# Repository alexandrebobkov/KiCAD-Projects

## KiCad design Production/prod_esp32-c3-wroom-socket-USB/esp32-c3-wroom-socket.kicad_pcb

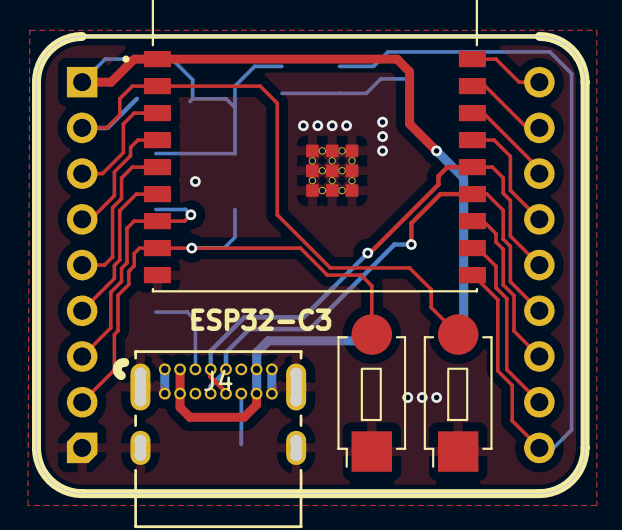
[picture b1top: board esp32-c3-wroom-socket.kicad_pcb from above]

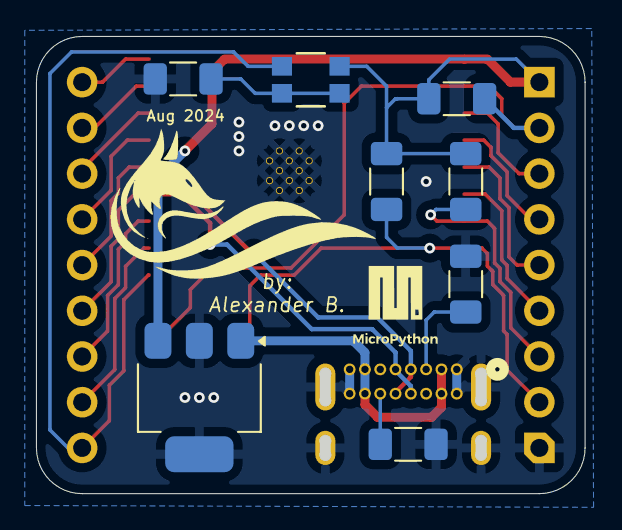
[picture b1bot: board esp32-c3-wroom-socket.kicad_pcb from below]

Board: 2 copper layers, 30.5 x 25.4 mm, 13 parts (8 on the bottom side), 22 nets.

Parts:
J2: Conn_ESP32-C3-WROOM-02
J4: USB-C_Receptacle_Data_16P_GCT-USB4085; USB-C GCT CONN16_USB4085-GF-A
LED1: LED-RED-GREEN-B1552USUG20D; B1552_HVK-M
R1: 10k; R_1206_3216Metric_Pad1.30x1.75mm_HandSolder
R4, R9, R10: 5k1; R_1206_3216Metric_Pad1.30x1.75mm_HandSolder
R7, R8: 2K2; R_1206_3216Metric_Pad1.30x1.75mm_HandSolder
SW1, SW2: SW_Push_SMD_6x3.5; SW_PUSH_6x3.5mm
U1: ESP32-C3-WROOM-02-N4; ESP32-C3-WROOM-02-H4
U2: AMS1117-3V3; SOT-223-3_TabPin2

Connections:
3V3: J2.1, LED1.2 (RED), R1.1, R7.1, R8.1, U1.1 (3V3), U2.3 (VO)
EN: J2.2, R1.2, SW2.2, U1.2 (EN)
GND: J2.9, J4.A1 (GND), J4.A12 (GND), J4.B1 (GND), J4.B12 (GND), J4.S1 (SHIELD), J4.S2 (SHIELD), J4.S3 (SHIELD), J4.S4 (SHIELD), R4.1, R9.1, R10.1, SW1.1, SW2.1, U1.9 (GND), U1.19 (GND__1), U1.20 (GND__2), U1.21 (GND__3), U1.22 (GND__4), U1.23 (GND__5), U1.24 (GND__6), U1.25 (GND__7), U1.26 (GND__8), U1.27 (GND__9), U1.28 (GND__10), U1.29 (GND__11), U1.30 (GND__12), U1.31 (GND__13), U1.32 (GND__14), U1.33 (GND__15), U1.34 (GND__16), U1.35 (GND__17), U1.36 (GND__18), U1.37 (GND__19), U1.38 (GND__20), U1.39 (GND__21), U2.2 (GND)
GPIO0: J2.18, U1.18 (IO0)
GPIO1: J2.17, U1.17 (IO1)
GPIO2: J2.16, U1.16 (IO2)
GPIO3: J2.15, U1.15 (IO3)
GPIO4: J2.3, U1.3 (IO4)
GPIO5: J2.4, U1.4 (IO5)
GPIO6: J2.5, U1.5 (IO6)
GPIO7: J2.6, U1.6 (IO7)
GPIO8: J2.7, R7.2, U1.7 (IO8)
GPIO9: J2.8, R8.2, SW1.2, U1.8 (IO9)
GPIO10: J2.10, LED1.3 (GRN), U1.10 (IO10)
unnamed: J4.A5 (CC1), R10.2
unnamed: J4.B5 (CC2), R9.2
unnamed: LED1.1 (GND), LED1.4 (GND), R4.2
UART-RX: J2.11, U1.11 (RXD)
UART-TX: J2.12, U1.12 (TXD)
USB_D+: J2.14, J4.A6 (D+), J4.B6 (D+), U1.14 (IO19)
USB_D-: J2.13, J4.A7 (D-), J4.B7 (D-), U1.13 (IO18)
VBUS: J4.A4 (VBUS), J4.A9 (VBUS), J4.B4 (VBUS), J4.B9 (VBUS), U2.1 (VI)

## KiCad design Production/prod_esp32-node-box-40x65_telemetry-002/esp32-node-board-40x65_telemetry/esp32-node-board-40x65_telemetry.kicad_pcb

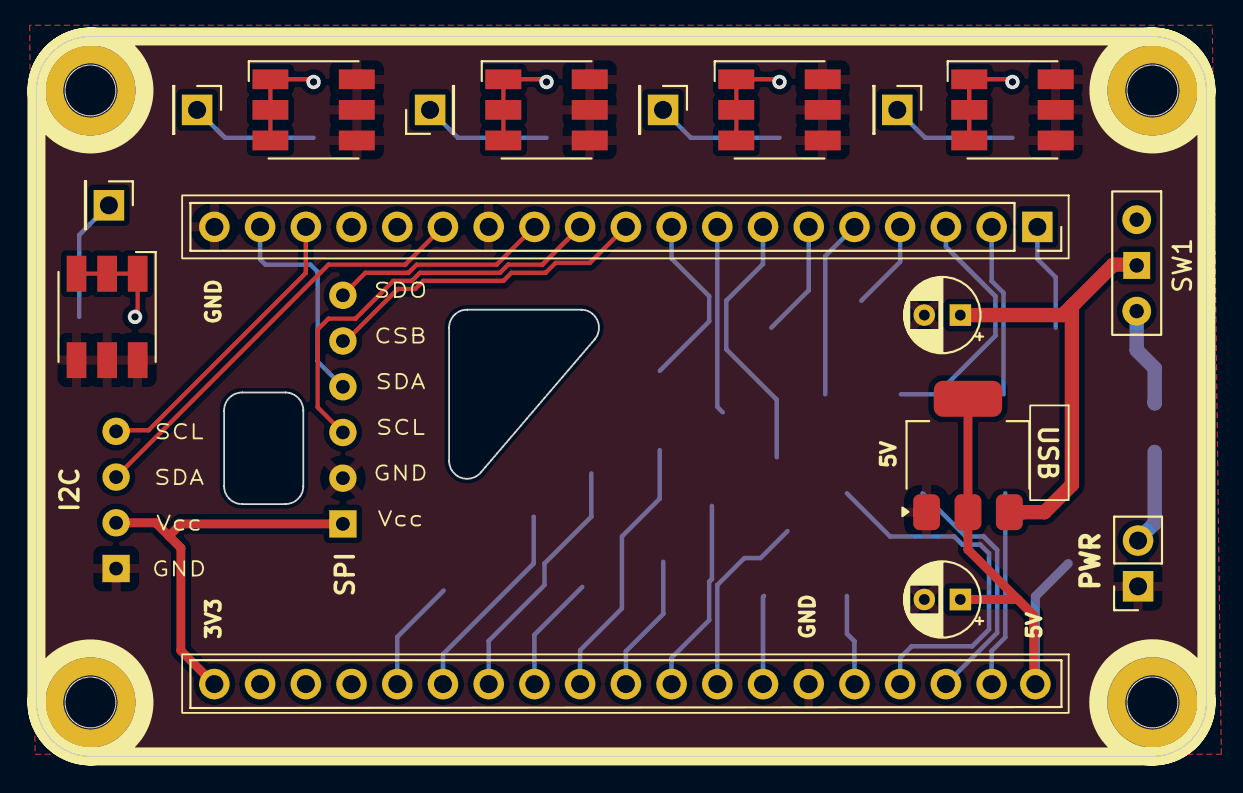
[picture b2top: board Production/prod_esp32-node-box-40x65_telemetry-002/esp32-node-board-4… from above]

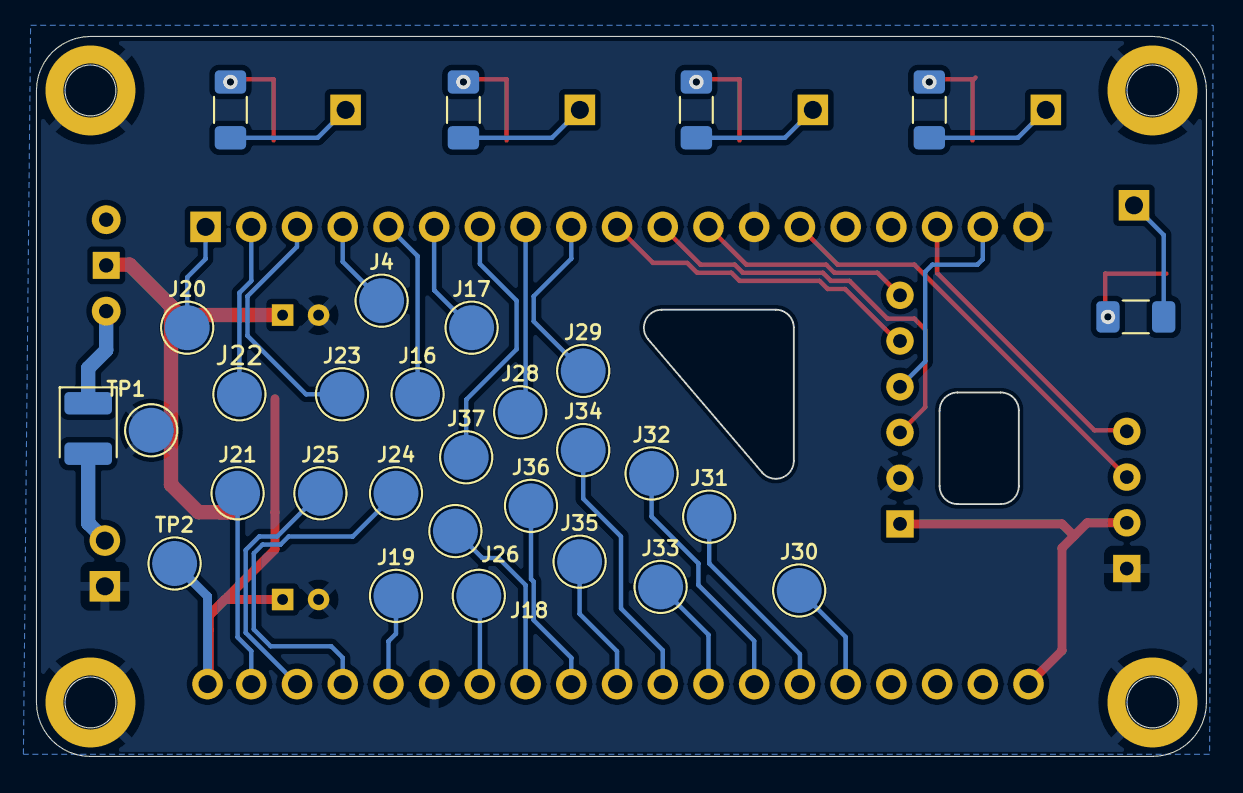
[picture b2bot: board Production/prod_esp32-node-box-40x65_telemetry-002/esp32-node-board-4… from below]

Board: 2 copper layers, 65.0 x 40.0 mm, 49 parts (30 on the bottom side), 44 nets.

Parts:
C1, C2: 1uF; CP_Radial_D4.0mm_P2.00mm
D1: D; D_1210_3225Metric
D2, D3, D4, D5, D6: LED_SMD_5050; LED_5050-6
H1: Project_Box_Board_65x40; Board_65-40
J1: PWR; PinSocket_1x02_P2.54
J3: I2C; Conn_I2C
J4: PIN-4; TestPoint_D2.5mm
J5: Conn_SPI
J6: Socket_LED3; PinHeader_1x01_P2.54mm_Vertical
J7: Socket_LED4; PinHeader_1x01_P2.54mm_Vertical
J8: Socket_LED5; PinHeader_1x01_P2.54mm_Vertical
J9: Conn_ESP32_WROOM-DevKit-38pins
J11: Socket_LED1; PinHeader_1x01_P2.54mm_Vertical
J12: Socket_LED2; PinHeader_1x01_P2.54mm_Vertical
J16: PIN-5; TestPoint_D2.5mm
J17: PIN-6; TestPoint_D2.5mm
J18: PIN-32; TestPoint_D2.5mm
J19: PIN-34; TestPoint_D2.5mm
J20: CLK; TestPoint_D2.5mm
J21: CMD; TestPoint_D2.5mm
J22: D0; TestPoint_D2.5mm
J23: D1; TestPoint_D2.5mm
J24: D2; TestPoint_D2.5mm
J25: D3; TestPoint_D2.5mm
J26: PIN-31; TestPoint_D2.5mm
J28: PIN-8; TestPoint_D2.5mm
J29: PIN-9; TestPoint_D2.5mm
J30: PIN-24; TestPoint_D2.5mm
J31: PIN-25; TestPoint_D2.5mm
J32: PIN-26; TestPoint_D2.5mm
J33: PIN-27; TestPoint_D2.5mm
J34: PIN-28; TestPoint_D2.5mm
J35: PIN-29; TestPoint_D2.5mm
J36: PIN-30; TestPoint_D2.5mm
J37: PIN-7; TestPoint_D2.5mm
R1, R2, R3, R4, R5: 5k1; R_1206_3216Metric_Pad1.30x1.75mm_HandSolder
SW1: SW_SPDT; SW_Slide-03_7.3x2.5x2.5_P2.54mm
TP1: GND; TestPoint_D2.5mm
TP2: 5V; TestPoint_D2.5mm
U1: AMS1117-5.0; SOT-223-3_TabPin2

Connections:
+3V3: J3.Vcc (VCC), J5.Vcc (VCC), J9.20 (3V3)
+5V: C2.1, J9.38 (5V), TP2.1, U1.2 (VO)
/CLK: J9.1 (CLK), J20.1
/CMD: J9.37 (CMD), J21.1
/D0: J9.2 (D0), J22.1
/D1: J9.3 (D1), J23.1
/D2: J9.35 (D2), J24.1
/D3: J9.36 (D3), J25.1
/PIN-4: J4.1, J9.4 (15)
/PIN-5: J9.5 (2), J16.1
/PIN-6: J9.6 (0), J17.1
/PIN-7: J9.7 (4), J37.1
/PIN-8: J9.8 (16), J28.1
/PIN-9: J9.9 (17), J29.1
/PIN-24: J9.24 (34), J30.1
/PIN-25: J9.25 (35), J31.1
/PIN-26: J9.26 (32), J32.1
/PIN-27: J9.27 (33), J33.1
/PIN-28: J9.28 (25), J34.1
/PIN-29: J9.29 (26), J35.1
/PIN-30: J9.30 (27), J36.1
/PIN-31: J9.31 (14), J26.1
/PIN-32: J9.32 (12), J18.1
/PIN-34: J9.34 (13), J19.1
/SCL-2: J3.SCL, J9.17 (22)
/SDA-2: J3.SDA, J9.14 (21)
/SPI-CSB: J5.CSB, J9.10 (5)
/SPI-SCL: J5.SCL, J9.11 (18)
/SPI-SDA: J5.SDA, J9.18 (23)
/SPI-SDO: J5.SDO, J9.12 (19)
/VDC: D1.1 (K), SW1.3 (B)
/VIN: C1.1, SW1.1 (COM), U1.3 (VI)
GND: C1.2, C2.2, D2.4 (KR), D2.5 (AG), D2.6 (KR), D3.4 (KR), D3.5 (AG), D3.6 (KR), D4.4 (KR), D4.5 (AG), D4.6 (KR), D5.4 (KR), D5.5 (AG), D5.6 (KR), D6.4 (KR), D6.5 (AG), D6.6 (KR), H1.1 (GND), H1.2 (GND), H1.3 (GND), H1.4 (GND), J1.1, J3.GND, J5.GND, J9.13 (GND), J9.19 (GND), J9.33 (GND), TP1.1, U1.1 (GND)
unnamed: D1.2 (A), J1.2
unnamed: D2.1 (AB), D2.2 (KB), D2.3 (AR), R1.1
unnamed: D3.1 (AB), D3.2 (KB), D3.3 (AR), R2.1
unnamed: D4.1 (AB), D4.2 (KB), D4.3 (AR), R3.1
unnamed: D5.1 (AB), D5.2 (KB), D5.3 (AR), R4.1
unnamed: D6.1 (AB), D6.2 (KB), D6.3 (AR), R5.1
unnamed: J6.1, R1.2
unnamed: J7.1, R2.2
unnamed: J8.1, R3.2
unnamed: J11.1, R4.2
unnamed: J12.1, R5.2

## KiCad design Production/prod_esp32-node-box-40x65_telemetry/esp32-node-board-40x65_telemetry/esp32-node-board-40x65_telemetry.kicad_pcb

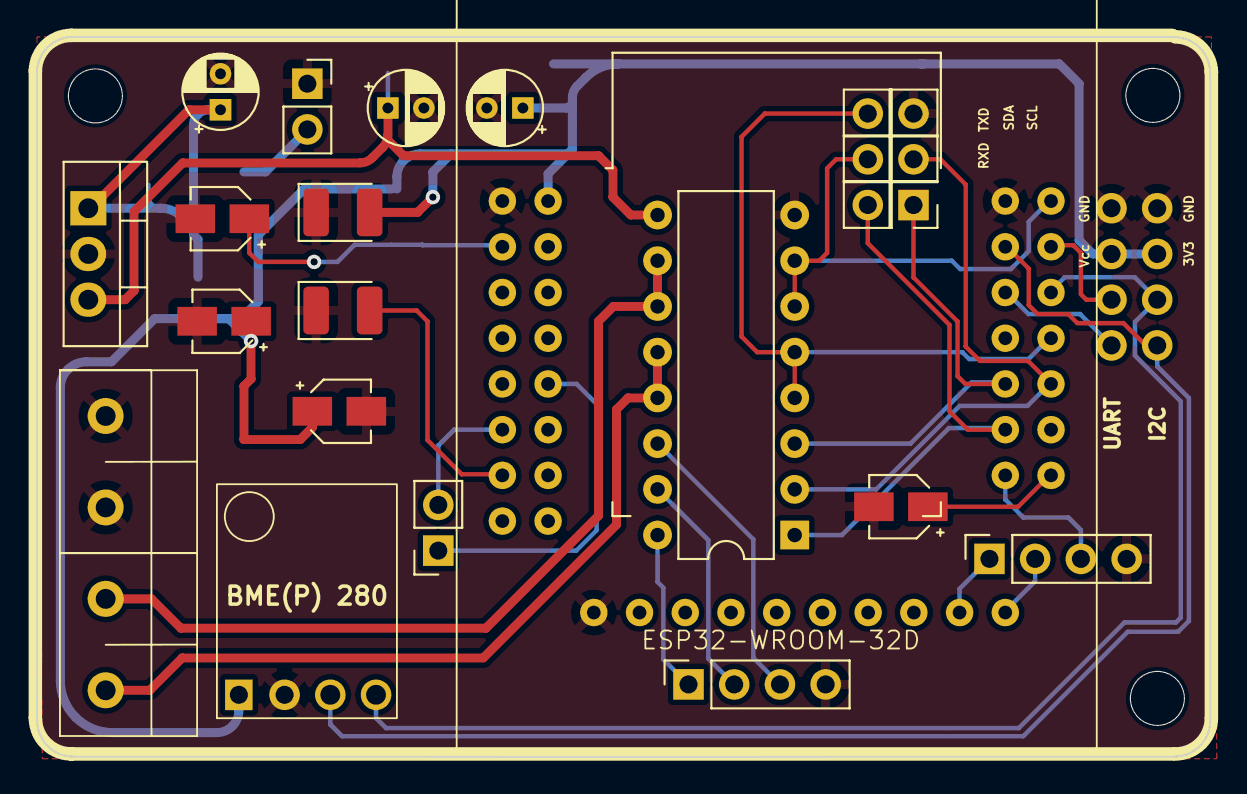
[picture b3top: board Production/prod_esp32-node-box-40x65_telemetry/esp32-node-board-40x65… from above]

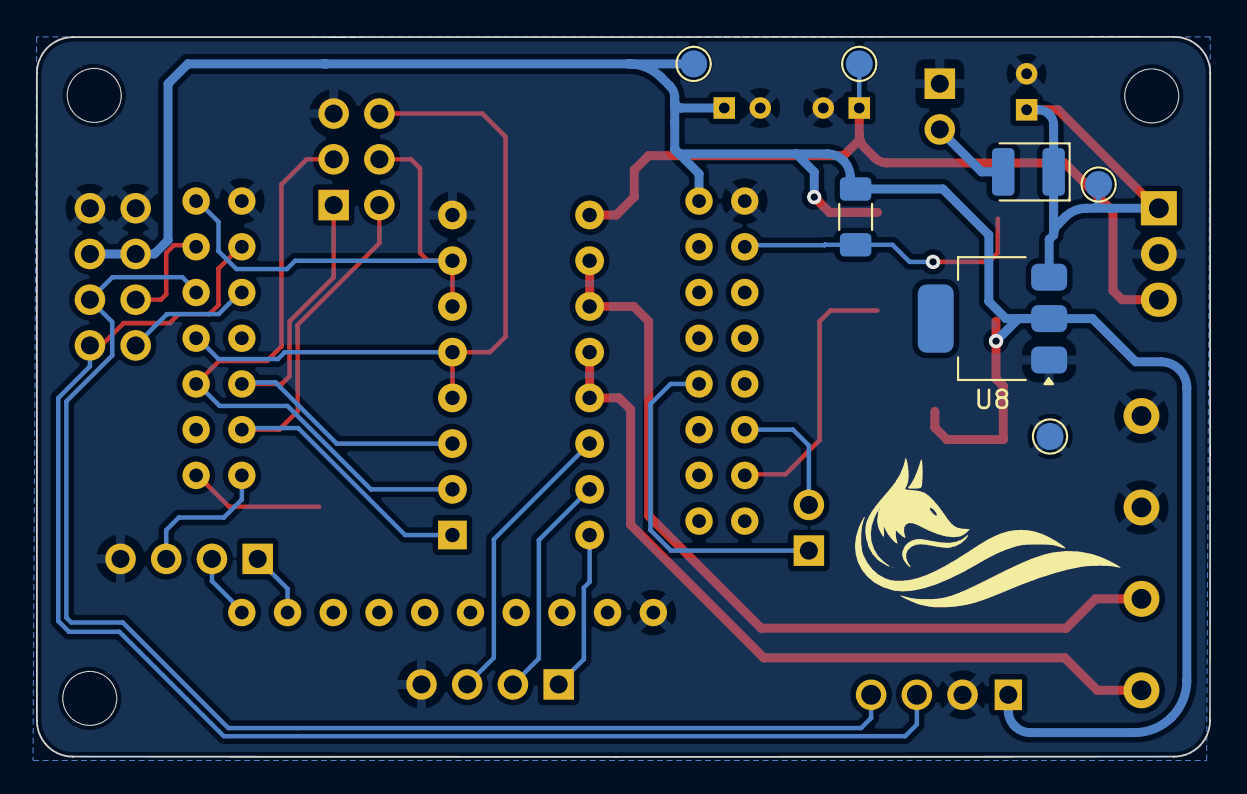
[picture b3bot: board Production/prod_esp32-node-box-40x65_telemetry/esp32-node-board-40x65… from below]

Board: 2 copper layers, 65.2 x 40.0 mm, 32 parts (7 on the bottom side), 27 nets.

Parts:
C1, C2, C3: 1uF; CP_Radial_D4.0mm_P2.00mm
C4, C5, C9: 0.1uF; CP_Elec_3x5.3
C8: 10uF; CP_Elec_3x5.3
D1: PWR; LED_1210_3225Metric_Pad1.42x2.65mm_HandSolder
D2: STATUS; LED_1210_3225Metric_Pad1.42x2.65mm_HandSolder
D4: D; D_1210_3225Metric
H1, H2, H4: MountingHole_Pad; MountingHole_3mm
J1: ESP32-WROOM-Adapter-Socket-2
J2: PWR; PinSocket_1x02_P2.54mm_Vertical
J3: UART; Conn_UART
J4: I2C; Conn_I2C
J5: DAC; PinSocket_1x02_P2.54mm_Vertical
J6: SOURCE; PinSocket_1x04_P2.54mm_Vertical
J8, J9: Conn_01x02_Socket; Conn_Terminal_5mm
J10: ADC; PinSocket_1x04_P2.54mm_Vertical
J14: GPIO; CONN_2x3
R1: 10K; R_1206_3216Metric_Pad1.30x1.75mm_HandSolder
TP1: VIN; TestPoint_Pad_D1.5mm
TP2: GND; TestPoint_Pad_D1.5mm
TP3: 3V3; TestPoint_Pad_D1.5mm
TP4: 5V; TestPoint_Pad_D1.5mm
U3: ULN2003; DIP-16_W7.62mm
U4: L7805; LD1117
U7: BME(P)280; BME280_BMP280_I2C
U8: AMS1117-3V3; AMS1117 SOT-223

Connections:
+3V3: C2.1, C8.1, C9.1, D1.2 (A), J1.2 (VDD), J3.3V3, J4.Vcc (VCC), R1.1, TP3.1, U7.1 (VDD), U8.2 (VO)
+5V: C3.1, TP4.1, U3.9 (COM), U4.3 (OUT)
/ADC2_CH0: J1.26 (IO4), J10.3
/ADC2_CH2: J1.24 (IO2), J10.2
/ADC2_CH3: J1.23 (IO15), J10.1
/BOOT: C5.1, J1.25 (IO0)
/DAC1: J1.10 (IO25), J5.1
/DAC2: J1.11 (IO26), J5.2
/EN: C4.1, J1.3 (EN), R1.2
/GPIO5: J1.29 (IO5), J14.2, U3.2 (I2)
/GPIO14: D2.2 (A), J1.13 (IO14)
/GPIO17: J1.28 (IO17), J14.4, U3.1 (I1)
/GPIO18: J1.30 (IO18), J14.1, U3.3 (I3)
/GPIO19: J1.31 (IO19), J14.6, U3.4 (I4), U3.5 (I5)
/GPIO23: J1.37 (IO23), J14.5, U3.6 (I6), U3.7 (I7)
/RXD: J1.34 (RXD0), J3.RXD
/SCL: J1.36 (SCL), J4.SCL, U7.3 (SCL)
/SDA: J1.33 (SDA), J4.SDA, U7.4 (SDA)
/SOURCE1: J8.2, U3.12 (O5), U3.13 (O4)
/SOURCE2: J8.1, U3.10 (O7), U3.11 (O6)
/SOURCE3: J6.1, U3.16 (O1)
/SOURCE4: J6.2, U3.15 (O2)
/SOURCE5: J6.3, U3.14 (O3)
/TXD: J1.35 (TXD0), J3.TXD
/VDC: D4.2 (A), J2.2
/VIN: C1.1, D4.1 (K), TP1.1, U4.1 (IN), U8.3 (VI)
GND: C1.2, C2.2, C3.2, C4.2, C5.2, C8.2, C9.2, D1.1 (K), D2.1 (K), J1.1 (GND), J1.15 (GND), J1.38 (GND), J2.1, J3.GND, J4.GND, J6.4, J9.1, J9.2, J10.4, J14.3, TP2.1, U3.8 (GND), U4.2 (GND), U7.2 (GND), U8.1 (ADJ)
